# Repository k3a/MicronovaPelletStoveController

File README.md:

# MicronovaPelletStoveController
My code and stuff to use when controlling Micronova Pellet Stove Controllers. Stufa a pellet Idro Aria telecomando.

Read the [full blog post](http://k3a.me/ir-controller-for-pellet-stove-with-micronova-controller-stufe-e-pellet-aria-ir-telecomando/).

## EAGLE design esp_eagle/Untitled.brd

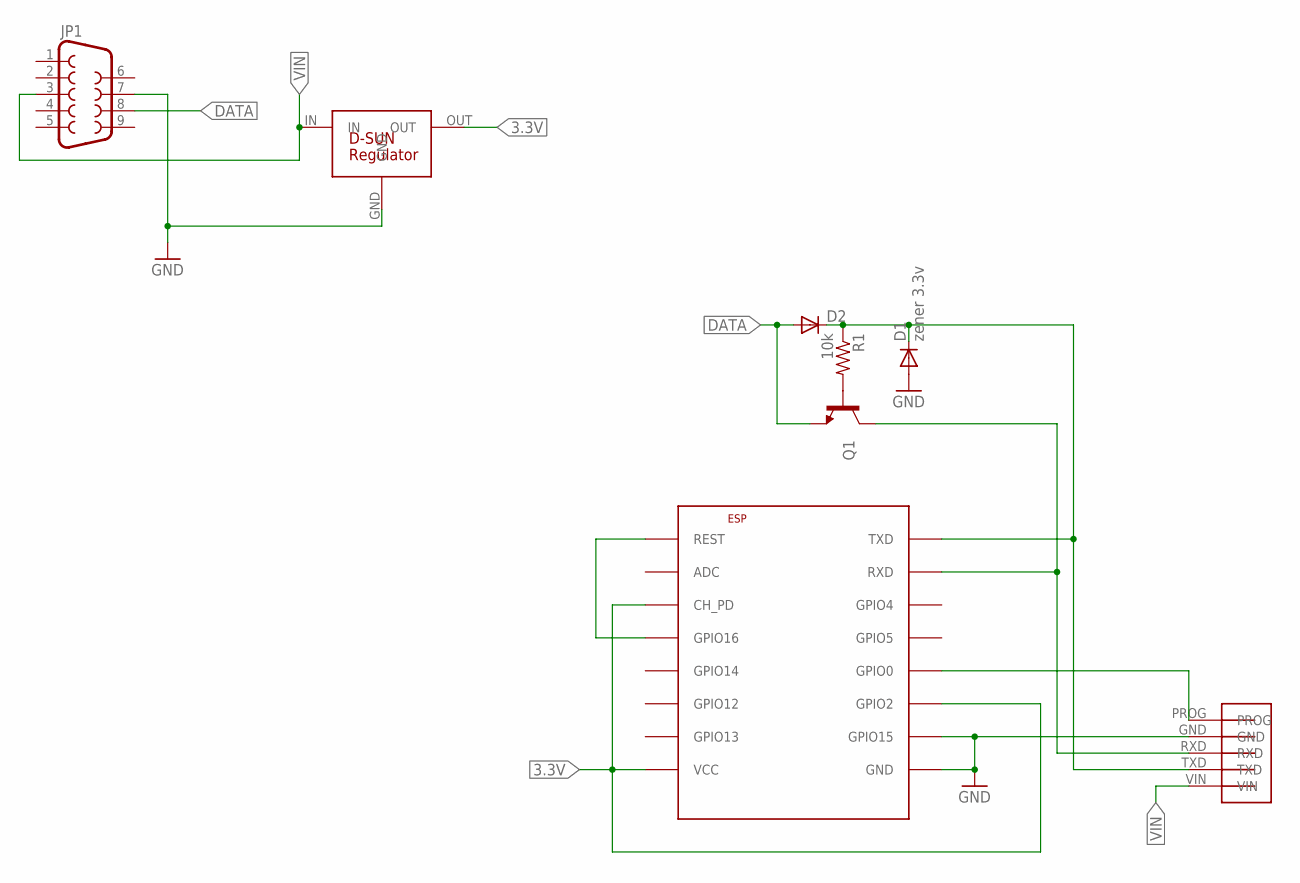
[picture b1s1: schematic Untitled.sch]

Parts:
D1: zener 3.3v; MINIMELF
D2: DIODE-MINIMELF; MINIMELF
ESP: ESP8266-07; ESP-07
JP1: DB9MALE; DB9_MALE
Q1: TRANSISTOR_NPNSOT23-3; SOT23-3
R1: 10k; 0805
U$3: ESPROG
U$4: D-SUN-REG

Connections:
3.3V: ESP.CH_PD, ESP.GPIO2, ESP.VCC, U$4.OUT
DATA: D2.A, JP1.8, Q1.2 (E)
GND: D1.A, ESP.GND, ESP.GPIO15, JP1.7, U$3.GND, U$4.GND
unnamed: D1.C, D2.C, ESP.TXD, R1.1, U$3.TXD
unnamed: ESP.RXD, Q1.3 (C), U$3.RXD
unnamed: ESP.GPIO0, U$3.PROG
unnamed: ESP.GPIO16, ESP.REST
unnamed: Q1.1 (B), R1.2
VIN: JP1.3, U$3.VIN, U$4.IN

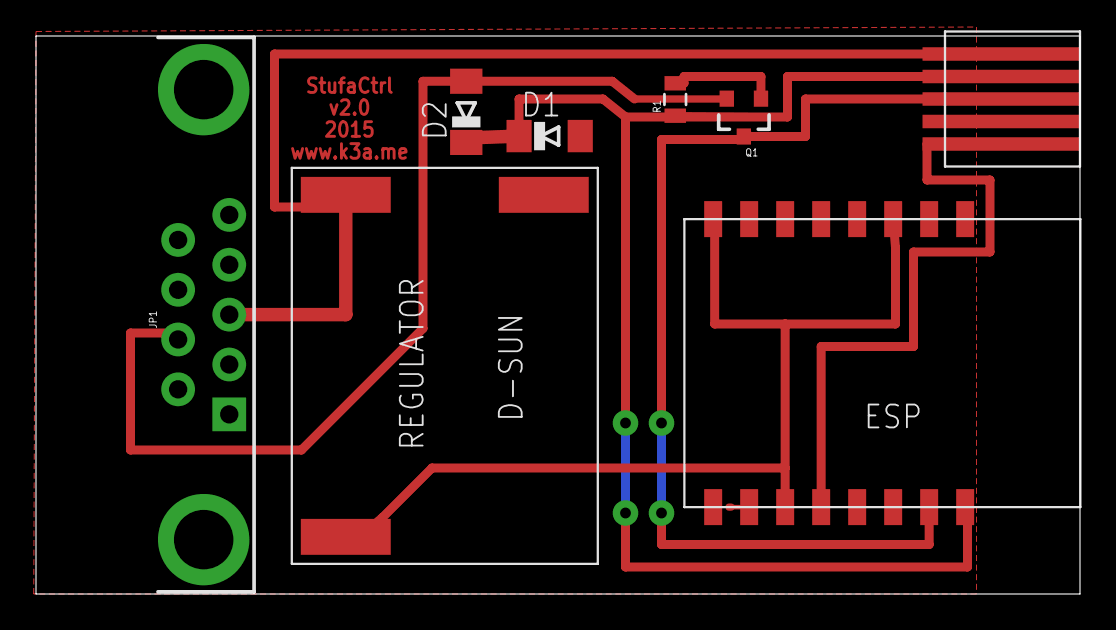
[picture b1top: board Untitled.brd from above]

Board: 2 copper layers, 58.0 x 31.0 mm, 8 parts (0 on the bottom side), 9 nets.

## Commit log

2015-10-03 added lcd arduino test code
2015-10-03 added lcd segment indices
2015-10-03 added arduino sketch for NC7WZ07 logic emulation
2015-10-03 added various pinouts
2015-10-03 added schematic of the interface
2015-10-03 added scope screens
2018-01-29 ESP8266 Eagle board
2018-12-11 arduino relay sketch
2018-12-13 LED pin define

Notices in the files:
parts and their libraries:
SparkFun-Connectors: Licensing: Creative Commons ShareAlike 4.0 International - https://creativecommons.org/licenses/by-sa/4.0
